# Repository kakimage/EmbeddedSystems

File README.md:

# EmbeddedSystems

Conjunto de projetos desenvolvidos para a disciplina de Projetos de Sistemas Embarcados do curso de Engenharia de Computação na Universidade Federal de Santa Catarina

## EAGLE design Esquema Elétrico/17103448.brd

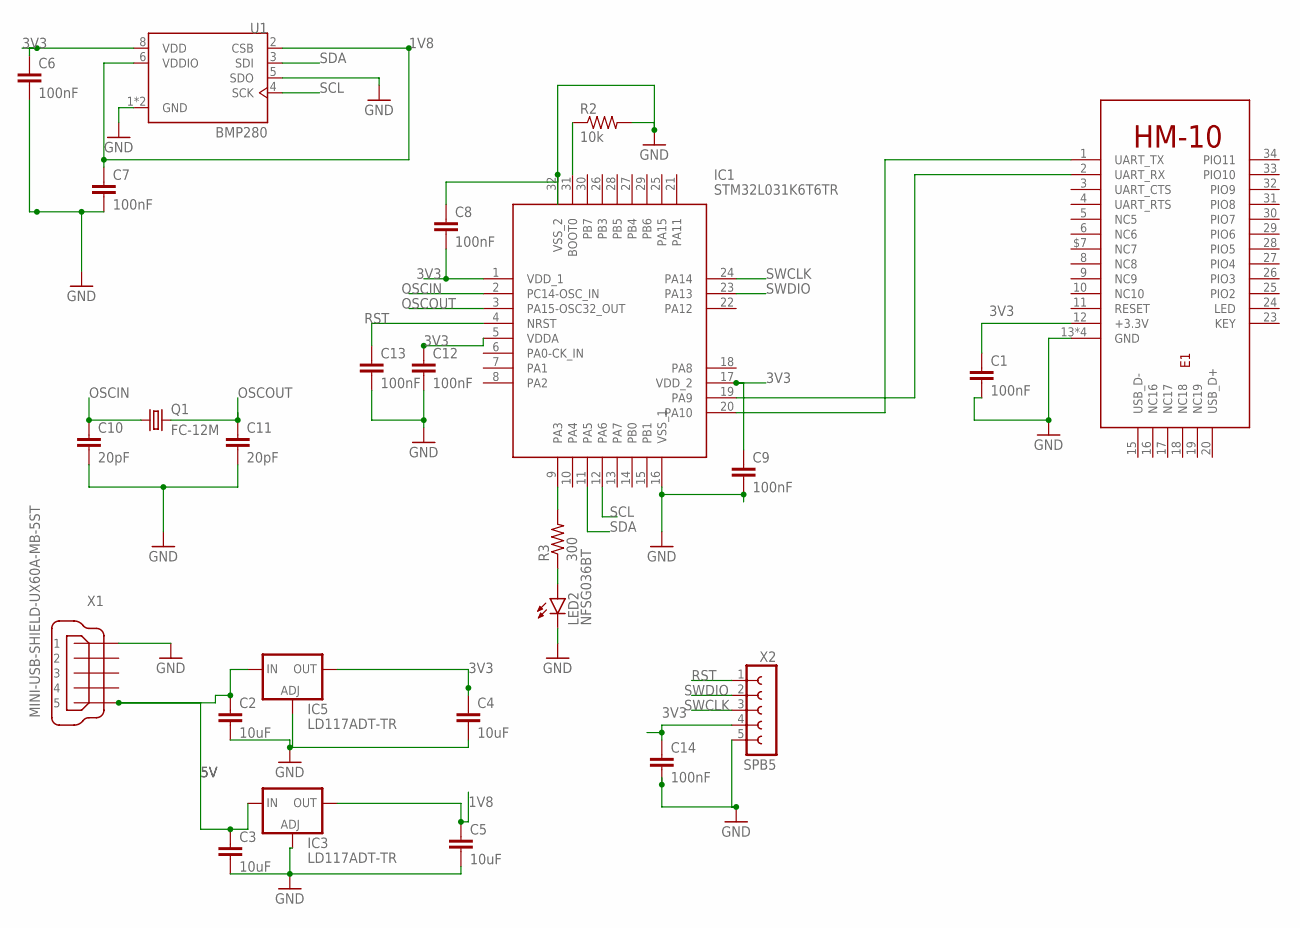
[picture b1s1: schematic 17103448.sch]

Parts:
C1, C6, C7, C8, C9, C12, C13, C14: 100nF; C0805
C2, C3, C4, C5: 10uF; C0805
C10, C11: 20pF; C0805
E1: HM-10-BOARD; 26.9X13X2.2_BOARD
IC1: STM32L031K6T6TR; QFP80P900X900X160-32N
IC3, IC5: LD117ADT-TR; DPACK
LED2: NFSG036BT
Q1: FC-12M
R2: 10k; R0805
R3: 300; R0805
U1: BMP280; XDCR_BMP280
X1: MINI-USB-SHIELD-UX60A-MB-5ST; UX60A-MB-5ST
X2: SPB5

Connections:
1V8: C5.1, C7.1, IC3.4 (OUT), U1.2 (CSB), U1.6 (VDDIO)
3V3: C1.1, C4.1, C6.1, C8.2, C9.1, C12.1, C14.1, E1.12 (+3.3V), IC1.1 (VDD_1), IC1.5 (VDDA), IC1.17 (VDD_2), IC5.4 (OUT), U1.8 (VDD), X2.4
5V: C2.1, C3.1, IC3.3 (IN), IC5.3 (IN), X1.5
GND: C1.2, C2.2, C3.2, C4.2, C5.2, C6.2, C7.2, C8.1, C9.2, C10.2, C11.2, C12.2, C13.2, C14.2, E1.13 (GND), E1.14 (GND), E1.21 (GND), E1.22 (GND), IC1.16 (VSS_1), IC1.32 (VSS_2), IC3.1 (ADJ), IC5.1 (ADJ), LED2.C, R2.2, U1.1 (GND), U1.5 (SDO), U1.7 (GND), X1.1, X2.5
unnamed: IC1.31 (BOOT0), R2.1
unnamed: E1.2 (UART_RX), IC1.19 (PA9)
unnamed: E1.1 (UART_TX), IC1.20 (PA10)
unnamed: LED2.A, R3.1
unnamed: IC1.9 (PA3), R3.2
OSCIN: C10.1, IC1.2 (PC14-OSC_IN), Q1.1
OSCOUT: C11.1, IC1.3 (PA15-OSC32_OUT), Q1.2
RST: C13.1, IC1.4 (NRST), X2.1
SCL: IC1.12 (PA6), U1.4 (SCK)
SDA: IC1.11 (PA5), U1.3 (SDI)
SWCLK: IC1.24 (PA14), X2.3
SWDIO: IC1.23 (PA13), X2.2

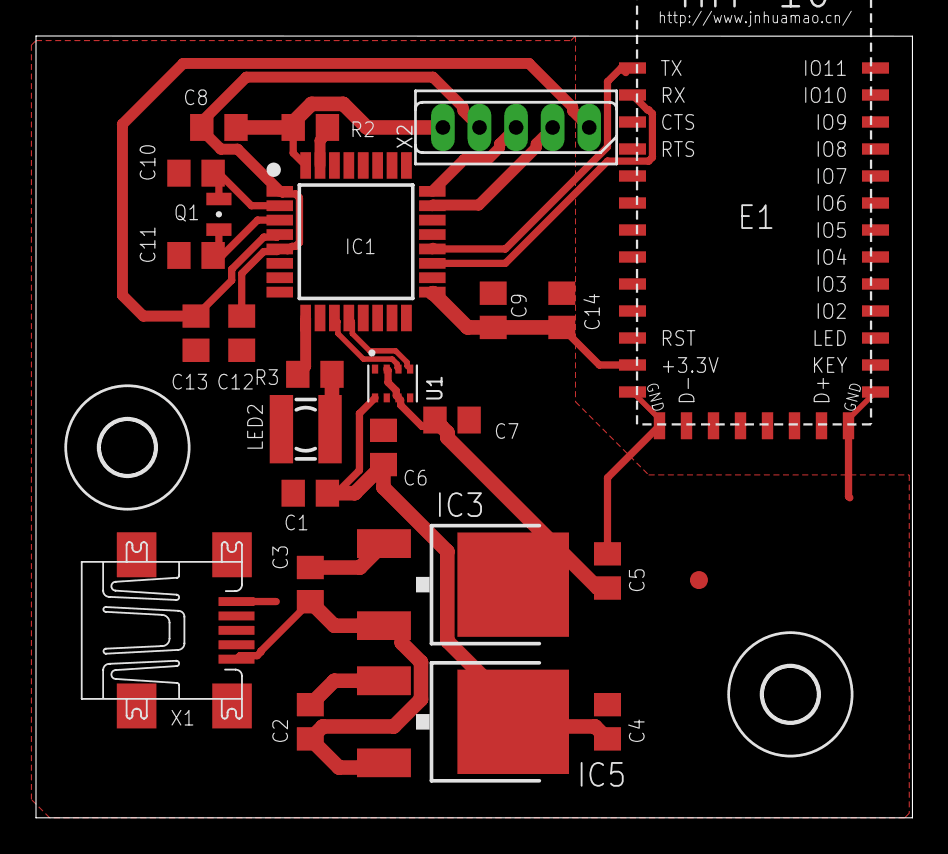
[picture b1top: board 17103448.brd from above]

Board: 2 copper layers, 48.7 x 43.4 mm, 28 parts (0 on the bottom side), 16 nets.

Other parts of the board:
U$1: FIDUCIAL_G10
U$2, U$3: 3,0

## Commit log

2022-07-08 adding files
2022-07-08 adding files from pc
2022-07-08 teste2'
2022-07-08 teste
2022-07-19 adding cpu_universal
2022-07-26 firmware raul e rian
2022-07-26 firmware final
2022-07-27 fixing drop

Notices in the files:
parts and their libraries:
dicons: Copyright (C) 2004, Bob Starr (rtzaudio@mindspring.com)
